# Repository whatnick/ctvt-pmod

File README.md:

# CTVT PMOD

CTVT PMOD is a compact, open-hardware analog front end for phase-coherent
current and voltage sampling. It uses a TI ADS131M02 dual 24-bit delta-sigma
ADC and is intended for energy-monitoring DSP experiments, including Tiny
Tapeout ASIC projects.

The routed KiCad 10 design is 30 mm x 70 mm with 3 mm corner radii and two
2.2 mm non-plated M2 mounting holes at the PMOD end. The PMOD connectors are
centered together on one short edge; the CT and AC/AC transformer inputs face
away from them at the opposite edge so adjacent PMODs remain usable. All
routed signals use 0.25 mm traces with 0.20 mm copper clearance.

The narrow layout keeps the measurement front end beside other PMODs rather
than blocking them. Both field connectors project beyond the board edge for
comfortable cable access, while the vertical female header provides a second
PMOD connection for stacking or logic-analyzer access.

| Component side | Rear silkscreen and routing |
|---|---|
|  |  |

## Digital companion

The [CTVT Energy DSP](https://github.com/whatnick/tt-ctvt-energy-dsp)
repository contains the companion Tiny Tapeout design. Its working first stage
captures ADS131M02 frames, performs time-shared multiply-accumulate operations,
generates the ADC clock and reset, and publishes coherent voltage, current,
active-power, RMS, and energy measurements over a separate host SPI interface.
The roadmap adds full ADC register configuration, gain/phase calibration,
power-quality events, and resource-efficient Goertzel harmonic analysis.

See [ADC PMOD comparative analysis](docs/adc-pmod-comparison.md) for a
comparison with the commercial ADC and mixed-signal boards listed in
[`docs/expansion_boards__daughter_cards.csv`](docs/expansion_boards__daughter_cards.csv),
including the AD7124-8 precision delta-sigma PMOD.

## Signal path

```text
CT jack -> split burden -> protection -> differential RC filter --+
                                                                   |
AC/AC jack -> balanced divider -> protection -> differential RC ---+-> ADS131M02
                                                                        |
3.3 V PMOD <---------------- SPI, DRDY, RESET, CLK ----------------------+
```

- **Current channel:** Same Sky `SJ-3523-SMT-TR` 3.5 mm stereo jack, with
  tip and sleeve as the differential CT input and ring grounded. Two 6.49 ohm
  0.1% burden resistors form a 12.98 ohm differential burden. The jack's
  mating face overhangs the field edge by 2.0 mm so a right-angle plug body
  clears the PCB.
- **Voltage channel:** Same Sky `PJ-002BH-SMT-TR` barrel jack for an isolated
  9-12 VAC transformer. Each leg uses a 100 kohm / 6.49 kohm balanced divider.
- **Filtering:** Each ADC channel has two 1 kohm series resistors and a 10 nF
  C0G differential capacitor, giving an approximate 8 kHz differential pole.
- **Assembly:** All chip passives are 0603 or larger and every fitted
  reference designator is present on silkscreen.
- **Protection:** `SMF3.3CA` on the CT input and `SMBJ18CA` on the transformer
  input.
- **Conversion:** ADS131M02 with filtered analog power, local decoupling,
  seven test points, and simultaneous voltage/current sampling.

## PMOD interface

J1 is the right-angle male peripheral connector. J4 is a vertical female
Wurth `61301221821` vertical pass-through socket; all twelve pins are connected
one-to-one for PMOD chaining.

| Pin | Signal | Direction at CTVT | Purpose |
|---:|---|---|---|
| 1 | CS | Input | SPI chip select |
| 2 | MOSI | Input | SPI data to ADC |
| 3 | MISO | Output | SPI data from ADC |
| 4 | SCLK | Input | SPI clock |
| 5 | GND | Power | Ground |
| 6 | +3V3 | Power | Regulated 3.3 V input |
| 7 | DRDY | Output | Conversion-ready interrupt |
| 8 | RESET | Input | ADC reset |
| 9 | CLK_HOST | Input | Optional external ADC clock |
| 10 | RESERVED | Pass-through | Reserved chained signal |
| 11 | GND | Power | Ground |
| 12 | +3V3 | Power | Regulated 3.3 V input |

The Tiny Tapeout companion maps the PMOD signals as follows:

| PMOD signal | Tiny Tapeout signal |
|---|---|
| CS | `uio[0]` |
| MOSI | `uio[1]` |
| MISO | `uio[2]` |
| SCLK | `uio[3]` |
| DRDY | `uio[4]` |
| RESET | `uio[5]` |
| CLK_HOST | `uio[6]` |

This standard Pmod ordering lets the board plug directly into the
bidirectional Tiny Tapeout/FabricFox connector. The host processor uses the
separate input and output ports, so it does not contend with the ADC bus.

## Scaling and calibration

The CT channel differential voltage is:

```text
V_CT_RMS = I_secondary_RMS x 12.98 ohm
```

For example, a 100 A : 50 mA CT produces approximately 0.649 Vrms at rated
primary current. Confirm the selected CT's maximum secondary current and
fault behavior before connection.

The voltage channel nominal divider ratio is:

```text
6.49 kohm / (100 kohm + 6.49 kohm) = 0.06095
```

A 9-12 Vrms isolated transformer therefore produces approximately
0.549-0.731 Vrms differential at the ADC input. Configure the ADS131M02 gain
for the resulting peak voltage and retain headroom for transformer regulation
and mains excursions.

Calibrate voltage gain, current gain, phase, and channel offset against a
traceable low-voltage source before calculating power. TP1-TP4 expose the four
ADC inputs; TP5 is DRDY, TP6 is +3V3, and TP7 is GND.

## Safety

**Use only an isolated CT and a certified isolated AC/AC transformer. Never
connect mains directly to this board.** The barrel jack is an isolated
low-voltage AC input, not a DC supply input. Enclosure, wiring, fusing,
creepage, clearance, and regulatory compliance remain the responsibility of
the final system.

## Build and outputs

Open `ctvt-pmod.kicad_pro` in KiCad 10. The committed schematic and PCB are
complete and routed. Project-local connector footprints and STEP models avoid
dependencies on the ATM90E26 FeatherWing repository.

The design sources are generated in this order:

```powershell
python scripts\generate_schematic.py
& "C:\Program Files\KiCad\10.0\bin\python.exe" scripts\generate_board.py
# Export a Specctra DSN, route it, and save the result as routing\ctvt-pmod.ses.
& "C:\Program Files\KiCad\10.0\bin\python.exe" scripts\finalize_route.py
```

`scripts/finalize_route.py` imports the saved Freerouting session, normalizes
all traces to at least 0.25 mm, verifies the stereo jack's generated 2.0 mm
mating-face overhang, adds the rear OSHW/Whatnick branding, and fills GND zones
on both copper layers. Run `scripts\adjust_stereo_jack.py` to verify the
overhang independently or
`scripts\add_branding.py` to reapply only the branding.
Run `scripts\add_mechanical_features.py` to reapply the 3 mm corner radii and
two M2 mounting holes without disturbing routed copper or manual silkscreen.
Manufacturing exports are generated into ignored `gerbers/` and `bom/`
directories. The reviewed orderable BOM and DigiKey sourcing notes are
committed in [`docs/ctvt-pmod-sourced-bom.csv`](docs/ctvt-pmod-sourced-bom.csv)
and [`docs/bom-sourcing.md`](docs/bom-sourcing.md).

Generate the Elecrow PCBA upload package with:

```powershell
python scripts\export_elecrow.py
```

This creates `manufacturing/elecrow/ctvt-pmod-elecrow-pcba.zip` containing a
Gerber ZIP, curated BOM, component position file, and current KiCad DRC/ERC
reports. See
[`docs/elecrow-manufacturing.md`](docs/elecrow-manufacturing.md) for package
contents and assembly-review notes.

## Repository contents

- `ctvt-pmod.kicad_sch` - complete schematic
- `ctvt-pmod.kicad_pcb` - routed two-layer PCB
- `ctvt-pmod.pretty/` - project-local barrel-jack and PMOD socket footprints
- `models/step/` - project-local connector STEP models
- `routing/ctvt-pmod.ses` - saved autorouter result
- `scripts/` - deterministic schematic, placement, and routing finalization

Licensed under CERN-OHL-S-2.0-or-later.

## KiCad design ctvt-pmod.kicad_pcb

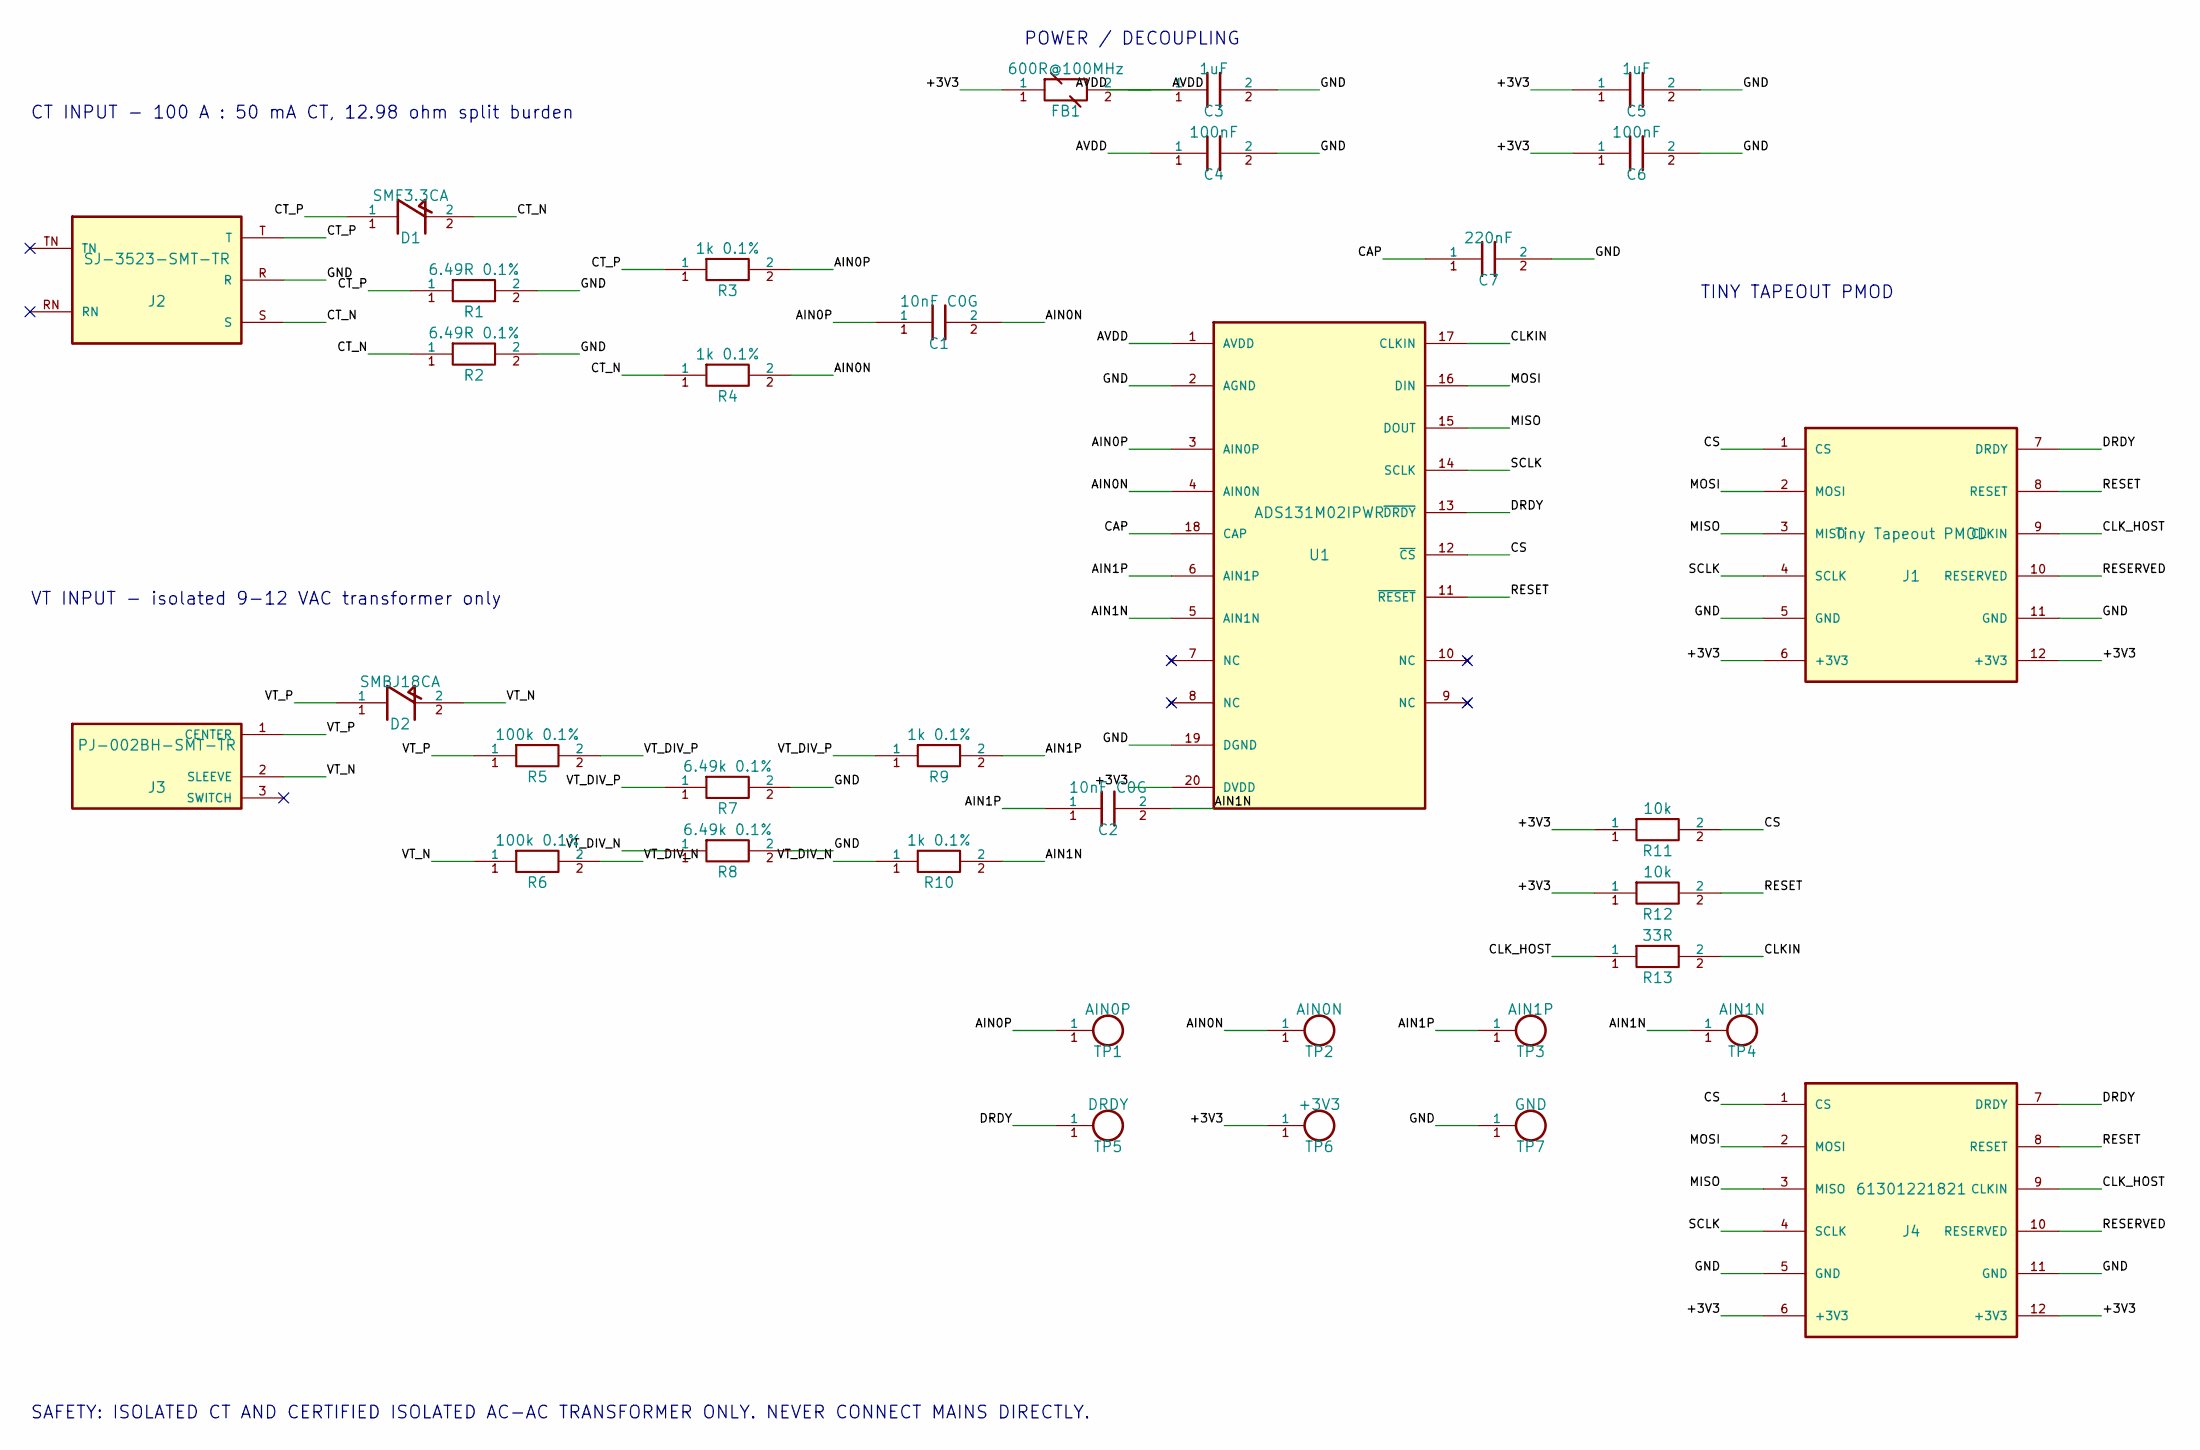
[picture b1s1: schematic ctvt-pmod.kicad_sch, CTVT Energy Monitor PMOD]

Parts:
C1, C2: 10nF C0G; C_0603_1608Metric; MPN GRM1885C1H103JA01D; DigiKey PN 490-9666-1-ND
C3, C5: 1uF; C_0603_1608Metric; MPN C0603C105K4RACTU; DigiKey PN 399-C0603C105K4RACTUCT-ND
C4, C6: 100nF; C_0603_1608Metric; MPN C0603C104K5RACTU; DigiKey PN 399-C0603C104K5RACTUCT-ND
C7: 220nF; C_0603_1608Metric; MPN C0603C224K4RACTU; DigiKey PN 399-C0603C224K4RACTUCT-ND
D1: SMF3.3CA; D_SOD-123F; MPN GSMF3.3CA; DigiKey PN 4786-GSMF3.3CACT-ND
D2: SMBJ18CA; D_SMB; MPN SMBJ18CA; DigiKey PN SMBJ18CALFCT-ND
FB1: 600R@100MHz; L_0603_1608Metric; MPN MPZ1608S601ATA00; DigiKey PN 445-MPZ1608S601ATA00CT-ND
J1: Tiny Tapeout PMOD; PinHeader_2x06_P2.54mm_Horizontal; MPN TSW-106-08-G-D-RA; DigiKey PN 612-TSW-106-08-G-D-RA-ND
J2: SJ-3523-SMT-TR; Jack_3.5mm_CUI_SJ-3523-SMT_Horizontal; MPN SJ-3523-SMT-TR; DigiKey PN CP-3523SJCT-ND
J3: PJ-002BH-SMT-TR; DC_BARREL_JACK_SMD_2MM; MPN PJ-002BH-SMT-TR; DigiKey PN CP-002BHPJCT-ND
J4: 61301221821; PinSocket_2x06_P2.54mm_PMODHost1A; MPN 61301221821; DigiKey PN 732-61301221821-ND
R1, R2: 6.49R 0.1%; R_0805_2012Metric; MPN RN73C2A6R49BTDF
R3, R4, R9, R10: 1k 0.1%; R_0603_1608Metric; MPN RG1608P-102-B-T5; DigiKey PN RG16P1.0KBCT-ND
R5, R6: 100k 0.1%; R_0805_2012Metric; MPN ERA-6AEB104V; DigiKey PN P100KDACT-ND
R7, R8: 6.49k 0.1%; R_0805_2012Metric; MPN RT0805BRD076K49L; DigiKey PN YAG1965CT-ND
R11, R12: 10k; R_0603_1608Metric; MPN RMCF0603FT10K0; DigiKey PN RMCF0603FT10K0CT-ND
R13: 33R; R_0603_1608Metric; MPN RC0603FR-0733RL; DigiKey PN 13-RC0603FR-0733RLCT-ND
TP1: AIN0P; TestPoint_Pad_D1.0mm
TP2: AIN0N; TestPoint_Pad_D1.0mm
TP3: AIN1P; TestPoint_Pad_D1.0mm
TP4: AIN1N; TestPoint_Pad_D1.0mm
TP5: DRDY; TestPoint_Pad_D1.0mm
TP6: +3V3; TestPoint_Pad_D1.0mm
TP7: GND; TestPoint_Pad_D1.0mm
U1: ADS131M02IPWR; TSSOP-20_4.4x6.5mm_P0.65mm; MPN ADS131M02IPWR; DigiKey PN 296-ADS131M02IPWRCT-ND

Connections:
+3V3: C5.1, C6.1, FB1.1, J1.6 (+3V3), J1.12 (+3V3), J4.6 (+3V3), J4.12 (+3V3), R11.1, R12.1, TP6.1, U1.20 (DVDD)
AIN0N: C1.2, R4.2, TP2.1, U1.4 (AIN0N)
AIN0P: C1.1, R3.2, TP1.1, U1.3 (AIN0P)
AIN1N: C2.2, R10.2, TP4.1, U1.5 (AIN1N)
AIN1P: C2.1, R9.2, TP3.1, U1.6 (AIN1P)
AVDD: C3.1, C4.1, FB1.2, U1.1 (AVDD)
CAP: C7.1, U1.18 (CAP)
CLKIN: R13.2, U1.17 (CLKIN)
CLK_HOST: J1.9 (CLKIN), J4.9 (CLKIN), R13.1
CS: J1.1 (CS), J4.1 (CS), R11.2, U1.12 (~CS)
CT_N: D1.2, J2.S, R2.1, R4.1
CT_P: D1.1, J2.T, R1.1, R3.1
DRDY: J1.7 (DRDY), J4.7 (DRDY), TP5.1, U1.13 (~DRDY)
GND: C3.2, C4.2, C5.2, C6.2, C7.2, J1.5 (GND), J1.11 (GND), J2.R, J4.5 (GND), J4.11 (GND), R1.2, R2.2, R7.2, R8.2, TP7.1, U1.2 (AGND), U1.19 (DGND)
MISO: J1.3 (MISO), J4.3 (MISO), U1.15 (DOUT)
MOSI: J1.2 (MOSI), J4.2 (MOSI), U1.16 (DIN)
RESERVED: J1.10 (RESERVED), J4.10 (RESERVED)
RESET: J1.8 (RESET), J4.8 (RESET), R12.2, U1.11 (~RESET)
SCLK: J1.4 (SCLK), J4.4 (SCLK), U1.14 (SCLK)
VT_DIV_N: R6.2, R8.1, R10.1
VT_DIV_P: R5.2, R7.1, R9.1
VT_N: D2.2, J3.2 (SLEEVE), R6.1
VT_P: D2.1, J3.1 (CENTER), R5.1

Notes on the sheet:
CT INPUT - 100 A : 50 mA CT, 12.98 ohm split burden
VT INPUT - isolated 9-12 VAC transformer only
POWER / DECOUPLING
TINY TAPEOUT PMOD
SAFETY: ISOLATED CT AND CERTIFIED ISOLATED AC-AC TRANSFORMER ONLY. NEVER CONNECT MAINS DIRECTLY.

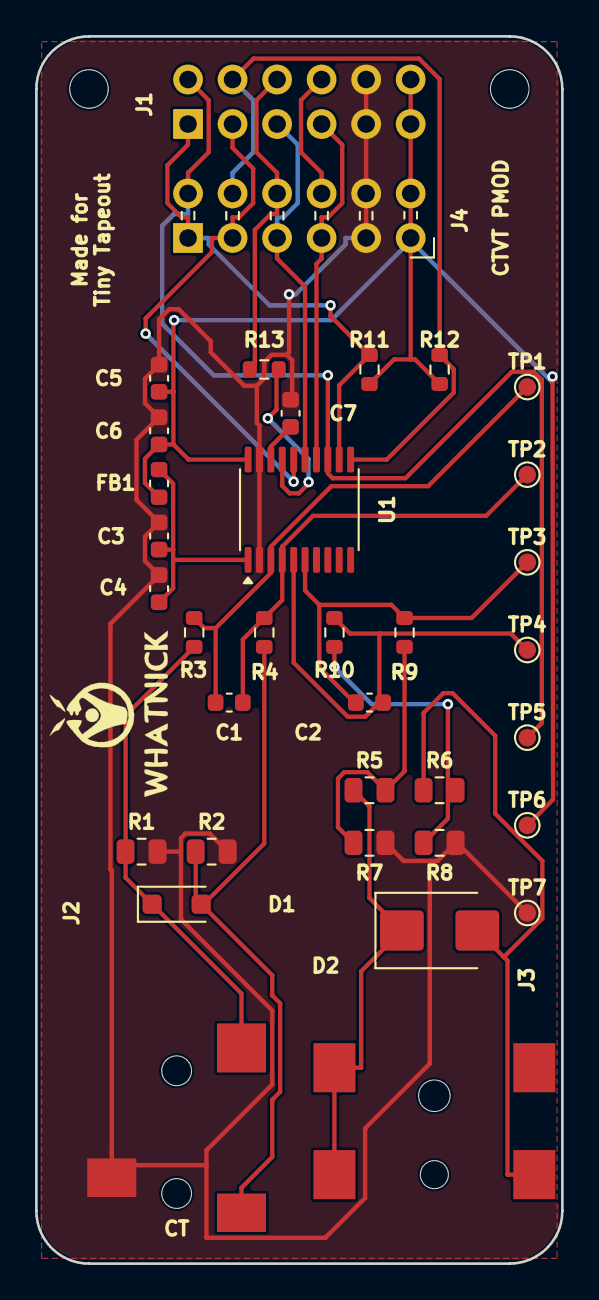
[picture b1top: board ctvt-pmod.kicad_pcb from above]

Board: 2 copper layers, 30.0 x 70.0 mm, 39 parts (1 on the bottom side), 23 nets.

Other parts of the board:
H1, H2: M2 mounting hole; MountingHole_2.2mm_M2
LOGO1: OSHW-LOGO-M
LOGO2: Whatnick_logo

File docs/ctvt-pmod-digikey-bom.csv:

References,Quantity,Value,Manufacturer,Manufacturer Part Number,DigiKey Part Number,Package,Sourcing Note
"C1 C2",2,10nF C0G,Murata Electronics,GRM1885C1H103JA01D,490-9666-1-ND,0603,50 V C0G 5%
"C3 C5",2,1uF,KEMET,C0603C105K4RACTU,399-C0603C105K4RACTUCT-ND,0603,16 V X7R 10%
"C4 C6",2,100nF,KEMET,C0603C104K5RACTU,399-C0603C104K5RACTUCT-ND,0603,50 V X7R 10%
C7,1,220nF,KEMET,C0603C224K4RACTU,399-C0603C224K4RACTUCT-ND,0603,16 V X7R 10%
D1,1,SMF3.3CA,Good-Ark Semiconductor,GSMF3.3CA,4786-GSMF3.3CACT-ND,SOD-123F,3.3 V bidirectional TVS
D2,1,SMBJ18CA,Littelfuse,SMBJ18CA,SMBJ18CALFCT-ND,DO-214AA SMB,18 V bidirectional TVS
FB1,1,600R@100MHz,TDK,MPZ1608S601ATA00,445-MPZ1608S601ATA00CT-ND,0603,600 ohm at 100 MHz
J1,1,Tiny Tapeout PMOD,Samtec,TSW-106-08-G-D-RA,612-TSW-106-08-G-D-RA-ND,2x6 2.54 mm THT,Right-angle male header
J2,1,SJ-3523-SMT-TR,Same Sky,SJ-3523-SMT-TR,CP-3523SJCT-ND,SMD,3.5 mm stereo jack
J3,1,PJ-002BH-SMT-TR,Same Sky,PJ-002BH-SMT-TR,CP-002BHPJCT-ND,SMD,2.5 x 5.5 mm barrel jack
J4,1,613012243121,Wurth Elektronik,613012243121,732-613012243121-ND,2x6 2.54 mm THT,Vertical female socket
"R1 R2",2,6.49R 0.1%,Vishay,TNPW08056R49BEEA,,0805,Not currently listed by DigiKey; do not substitute 1% without recalibration
"R3 R4 R9 R10",4,1k 0.1%,Susumu,RG1608P-102-B-T5,RG16P1.0KBCT-ND,0603,25 ppm/C thin film
"R5 R6",2,100k 0.1%,Panasonic Industry,ERA-6AEB104V,P100KDACT-ND,0805,25 ppm/C thin film
"R7 R8",2,6.49k 0.1%,Yageo,RT0805BRD076K49L,YAG1965CT-ND,0805,25 ppm/C thin film
"R11 R12",2,10k 1%,Stackpole Electronics,RMCF0603FT10K0,RMCF0603FT10K0CT-ND,0603,General-purpose
R13,1,33R 1%,Yageo,RC0603FR-0733RL,13-RC0603FR-0733RLCT-ND,0603,General-purpose
U1,1,ADS131M02IPWR,Texas Instruments,ADS131M02IPWR,296-ADS131M02IPWRCT-ND,TSSOP-20,24-bit dual-channel ADC

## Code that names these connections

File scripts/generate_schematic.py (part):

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
    # Connector labels and no-connects.
    blocks += [
        wire_label(2100, 1600, "CT_P"),
        wire_label(2100, 1800, "GND"),
        wire_label(2100, 2000, "CT_N"),
        no_connect(900, 1650),
        no_connect(900, 1950),
        wire_label(2100, 3950, "VT_P"),
        wire_label(2100, 4150, "VT_N"),
        no_connect(2100, 4250),
        # Input protection.
        wire_label(2400, 1500, "CT_P", -1),
        wire_label(3000, 1500, "CT_N"),
        wire_label(2350, 3800, "VT_P", -1),
        wire_label(2950, 3800, "VT_N"),
        # CT split burden and filter.
        wire_label(2700, 1850, "CT_P", -1),
        wire_label(3300, 1850, "GND"),
        wire_label(2700, 2150, "CT_N", -1),
        wire_label(3300, 2150, "GND"),
        wire_label(3900, 1750, "CT_P", -1),
        wire_label(4500, 1750, "AIN0P"),
        wire_label(3900, 2250, "CT_N", -1),
        wire_label(4500, 2250, "AIN0N"),
        wire_label(4900, 2000, "AIN0P", -1),
        wire_label(5500, 2000, "AIN0N"),
        # VT balanced divider and filter.
        wire_label(3000, 4050, "VT_P", -1),
        wire_label(3600, 4050, "VT_DIV_P"),
        wire_label(3000, 4550, "VT_N", -1),
        wire_label(3600, 4550, "VT_DIV_N"),
        wire_label(3900, 4200, "VT_DIV_P", -1),
        wire_label(4500, 4200, "GND"),
        wire_label(3900, 4500, "VT_DIV_N", -1),
        wire_label(4500, 4500, "GND"),
        wire_label(4900, 4050, "VT_DIV_P", -1),
        wire_label(5500, 4050, "AIN1P"),
        wire_label(4900, 4550, "VT_DIV_N", -1),
        wire_label(5500, 4550, "AIN1N"),
        wire_label(5700, 4300, "AIN1P", -1),
        wire_label(6300, 4300, "AIN1N"),
        # ADC pins.
        wire_label(6300, 2100, "AVDD", -1),
        wire_label(6300, 2300, "GND", -1),
        wire_label(6300, 2600, "AIN0P", -1),
        wire_label(6300, 2800, "AIN0N", -1),
        wire_label(6300, 3200, "AIN1P", -1),
        wire_label(6300, 3400, "AIN1N", -1),
        no_connect(6300, 3600),
        no_connect(6300, 3800),
        wire_label(6300, 3000, "CAP", -1),
        wire_label(6300, 4000, "GND", -1),
        wire_label(6300, 4200, "+3V3", -1),
        wire_label(7700, 2100, "CLKIN"),
        wire_label(7700, 2300, "MOSI"),
        wire_label(7700, 2500, "MISO"),
        wire_label(7700, 2700, "SCLK"),
        wire_label(7700, 2900, "DRDY"),
        wire_label(7700, 3100, "CS"),
        wire_label(7700, 3300, "RESET"),
        no_connect(7700, 3600),
        no_connect(7700, 3800),
        # Supply filtering and decoupling.
        wire_label(5500, 900, "+3V3", -1),
        wire_label(6100, 900, "AVDD"),
        wire_label(6200, 900, "AVDD", -1),
        wire_label(6800, 900, "GND"),
        wire_label(6200, 1200, "AVDD", -1),
        wire_label(6800, 1200, "GND"),
        wire_label(8200, 900, "+3V3", -1),
        wire_label(8800, 900, "GND"),
        wire_label(8200, 1200, "+3V3", -1),
        wire_label(8800, 1200, "GND"),
        wire_label(7500, 1700, "CAP", -1),
        wire_label(8100, 1700, "GND"),
        # Pull-ups and clock damping.
        wire_label(8300, 4400, "+3V3", -1),
        wire_label(8900, 4400, "CS"),
        wire_label(8300, 4700, "+3V3", -1),
        wire_label(8900, 4700, "RESET"),
        wire_label(8300, 5000, "CLK_HOST", -1),
        wire_label(8900, 5000, "CLKIN"),
        # PMOD physical pin numbering: 1-4 and 7-10 signals, 5/11 GND, 6/12 3V3.
        wire_label(9100, 2600, "CS", -1),
        wire_label(9100, 2800, "MOSI", -1),
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        wire_label(9100, 3200, "SCLK", -1),
        wire_label(9100, 3400, "GND", -1),
        wire_label(9100, 3600, "+3V3", -1),
        wire_label(10500, 2600, "DRDY"),
        wire_label(10500, 2800, "RESET"),
        wire_label(10500, 3000, "CLK_HOST"),
        wire_label(10500, 3200, "RESERVED"),
        wire_label(10500, 3400, "GND"),
        wire_label(10500, 3600, "+3V3"),
        # Female PMOD pass-through.
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        wire_label(9100, 6300, "SCLK", -1),
        wire_label(9100, 6500, "GND", -1),
        wire_label(9100, 6700, "+3V3", -1),
        wire_label(10500, 5700, "DRDY"),
        wire_label(10500, 5900, "RESET"),
        wire_label(10500, 6100, "CLK_HOST"),
        wire_label(10500, 6300, "RESERVED"),
        wire_label(10500, 6500, "GND"),
        wire_label(10500, 6700, "+3V3"),
        # Test points.
        wire_label(5750, 5350, "AIN0P", -1),
        wire_label(6750, 5350, "AIN0N", -1),
        wire_label(7750, 5350, "AIN1P", -1),
        wire_label(8750, 5350, "AIN1N", -1),
        wire_label(5750, 5800, "DRDY", -1),
        wire_label(6750, 5800, "+3V3", -1),
        wire_label(7750, 5800, "GND", -1),
        note(900, 1050, "CT INPUT - 100 A : 50 mA CT, 12.98 ohm split burden"),
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

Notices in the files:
ctvt-pmod.kicad_pcb:
REV 1.0 | CERN-OHL-S-2.0+
